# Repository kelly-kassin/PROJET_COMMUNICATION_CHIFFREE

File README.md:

# Projet_PCB_FISE_5A_POLYTECH : Communication IR Cryptée
# Binome : Kelly KASSIN & Youssef OMMI

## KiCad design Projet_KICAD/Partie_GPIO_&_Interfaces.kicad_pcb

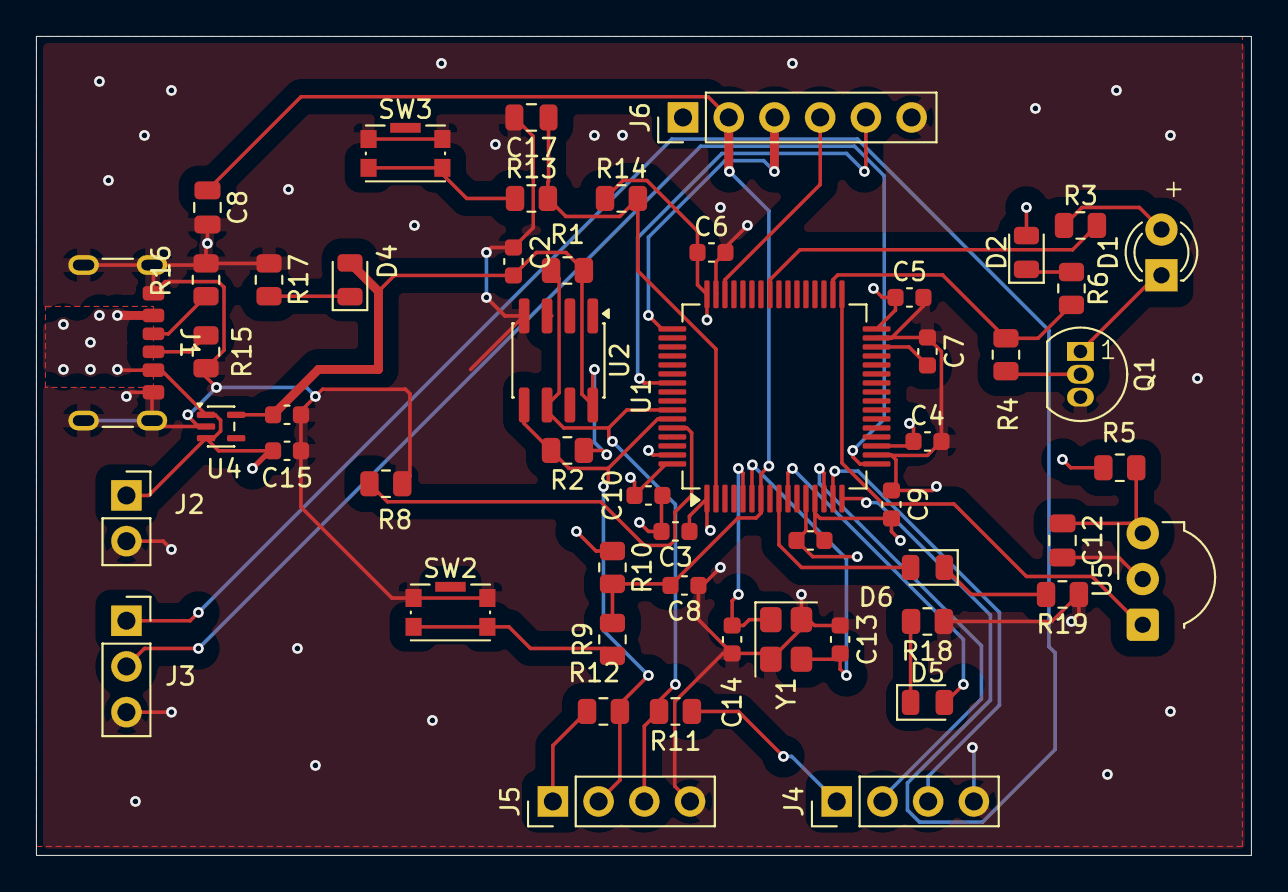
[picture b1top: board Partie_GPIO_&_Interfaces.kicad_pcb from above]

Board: 4 copper layers, 67.5 x 45.5 mm, 54 parts (0 on the bottom side), 35 nets.

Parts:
C2, C4, C5, C6, C8, C10, C11: 100nF; C_0603_1608Metric
C3: 4.7 uF; C_0603_1608Metric
C7: 4.7uF; C_0603_1608Metric
C8#2, C12, C17: 100nF; C_0805_2012Metric
C9: 2.2uF; C_0603_1608Metric
C13, C14: 20nF; C_0603_1608Metric
C15, C16: 1uF; C_0603_1608Metric
D1: TSAL4400; LED_D3.0mm_IRBlack
D2: LED GREEN; LED_0805_2012Metric
D4: LED RED; LED_0805_2012Metric
D5: LED YELLOW; LED_0805_2012Metric
D6: LED BLUE; LED_0805_2012Metric
J1: USB4125-GF-A-0190; USB_C_Receptacle_GCT_USB4125-xx-x-0190_6P_TopMnt_Horizontal
J2: Conn_01x02_Pin; PinSocket_1x02_P2.54mm_Vertical
J3: Conn_01x03_Pin; PinSocket_1x03_P2.54mm_Vertical
J4, J5: Conn_01x04_Pin; PinHeader_1x04_P2.54mm_Vertical
J6: Conn_01x06_Pin; PinHeader_1x06_P2.54mm_Vertical
Q1: 2N3906; TO-92_Inline
R1, R2, R11, R12: 4.7k; R_0805_2012Metric
R3, R4, R6, R9, R13, R17, R18, R19: 330; R_0805_2012Metric
R5: 100; R_0805_2012Metric
R8, R10, R14: 10k; R_0805_2012Metric
R15: 5.1K; R_0805_2012Metric
R16: 5.1k; R_0805_2012Metric
SW2, SW3: SW_Push; SW_Push_1P1T-SH_NO_CK_KMR2xxG
U1: STM32F413RGT6; LQFP-64_10x10mm_P0.5mm
U2: ATECC608C; SOIC-8_3.9x4.9mm_P1.27mm
U4: MIC5365-3.3YC5; SOT-353_SC-70-5
U5: TSOP34138; Vishay_MOLD-3Pin
Y1: Y322518.432MLBCX; Crystal_SMD_3225-4Pin_3.2x2.5mm

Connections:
+3.3V: C2.1, C3.1, C4.1, C5.1, C6.1, C9.1, C10.1, C11.1, C16.1, D2.2 (A), D4.2 (A), J4.1, J5.1, J6.1, R1.1, R2.1, R5.1, R10.1, R11.1, R12.1, R14.1, U1.1 (VBAT), U1.13 (VDDA), U1.19 (VDD), U1.32 (VDD), U1.48 (VDD), U1.64 (VDD), U2.8 (VCC), U4.5 (VOUT)
/GPIO_EXTI13: C17.1, R13.2, R14.2, U1.2 (PC13)
/HSE_IN: C14.2, U1.5 (PH0), Y1.1
/HSE_OUT: C13.2, U1.6 (PH1), Y1.3
/I2C1_SCL: J5.3, R1.2, R11.2, U1.58 (PB6), U2.6 (SCL)
/I2C1_SDA: J5.2, R2.2, R12.2, U1.59 (PB7), U2.5 (SDA)
/IR_RX: U1.33 (PB12), U5.1 (OUT)
/IR_TX: R4.2, R6.1, U1.34 (PB13)
/LED_IR_RX: D6.2 (A), U1.9 (PC1)
/NRST: C8.2, C8#2.1, J6.2, R9.2, R10.2, U1.7 (NRST)
/PWM: R3.2, U1.41 (PA8)
/SW_BOOT0: R8.1, U1.60 (BOOT0)
/SYS_JTDCK_SWDCLK: J6.3, U1.49 (PA14)
/SYS_JTDMS-SWDIO: J6.4, U1.46 (PA13)
/SYS_JTDO_SWDO: J6.5, U1.55 (PB3)
/UART2_RX: J3.2, U1.17 (PA3)
/UART2_TX: J3.1, U1.16 (PA2)
/UART4_RX: J4.3, U1.15 (PA1)
/UART4_TX: J4.2, U1.14 (PA0)
/VUSB: C15.1, J1.A9 (VBUS), J1.B9 (VBUS), J2.1, U4.1 (VIN), U4.3 (EN)
GND: C2.2, C3.2, C4.2, C5.2, C6.2, C7.2, C8.1, C8#2.2, C9.2, C10.2, C11.2, C12.2, C13.1, C14.1, C15.2, C16.2, C17.2, J1.A12 (GND), J1.B12 (GND), J1.SH (SHIELD), J2.2, J3.3, J4.4, J5.4, J6.6, Q1.3 (C), R8.2, R15.1, R16.1, R17.1, R18.1, R19.1, SW2.1, SW3.1, U1.12 (VSSA), U1.18 (VSS), U1.31 (VSS), U1.47 (VSS), U1.63 (VSS), U2.4 (GND), U4.2 (GND), U5.2 (GND), Y1.2 (G), Y1.4 (G)
unnamed: D1.2 (A), R3.1
unnamed: D1.1 (K), Q1.1 (E)
unnamed: D2.1 (K), R6.2
unnamed: D4.1 (K), R17.2
unnamed: D5.2 (A), U1.10 (PC2)
unnamed: D5.1 (K), R18.2
unnamed: D6.1 (K), R19.2
unnamed: J1.A5 (CC1), R16.2
unnamed: J1.B5 (CC2), R15.2
unnamed: Q1.2 (B), R4.1
unnamed: R9.1, SW2.2
unnamed: R13.1, SW3.2
unnamed: C7.1, U1.30 (VCAP_1)
unnamed: C12.1, R5.2, U5.3 (Vs)

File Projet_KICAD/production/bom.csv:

Designator,Footprint,Quantity,Value,LCSC Part #
"C10, C11, C2, C4, C5, C6, C8_2",0603,7,100nF,
"C12, C17, C8",0805,3,100nF,
"C13, C14",0603,2,20nF,
"C15, C16",0603,2,1uF,
C3,0603,1,4.7 uF,
C7,0603,1,4.7uF,
C9,0603,1,2.2uF,
D1,LED_D3.0mm_IRBlack,1,TSAL4400,
D2,0805,1,LED GREEN,C2297
D4,0805,1,LED RED,
D5,0805,1,LED YELLOW,
D6,0805,1,LED BLUE,
J1,USB_C_Receptacle_GCT_USB4125-xx-x-0190_6P_TopMnt_Horizontal,1,USB4125-GF-A-0190,
J2,PinSocket_1x02_P2.54mm_Vertical,1,Conn_01x02_Pin,C49661
J3,PinSocket_1x03_P2.54mm_Vertical,1,Conn_01x03_Pin,C22373889
"J4, J5",PinHeader_1x04_P2.54mm_Vertical,2,Conn_01x04_Pin,C32713270
J6,PinHeader_1x06_P2.54mm_Vertical,1,Conn_01x06_Pin,C32713272
Q1,TO-92_Inline,1,2N3906,
"R1, R2",0805,2,4.7k,C17673
"R10, R14, R8",0805,3,10k,C17414
"R11, R12",0805,2,4.7k,
"R13, R17, R18, R19, R3, R4, R6, R9",0805,8,330,C17630
R15,0805,1,5.1K,C26023
R16,0805,1,5.1k,C27834
R5,0805,1,100, C17408
"SW2, SW3",SW_Push_1P1T-SH_NO_CK_KMR2xxG,2,SW_Push,C269272
U1,LQFP-64_10x10mm_P0.5mm,1,STM32F413RGT6,
U2,SOIC-8_3.9x4.9mm_P1.27mm,1,ATECC608C,C25469796
U4,SOT-353_SC-70-5,1,MIC5365-3.3YC5,C3021118
U5,Vishay_MOLD-3Pin,1,TSOP34138,C118303
Y1,Crystal_SMD_3225-4Pin_3.2x2.5mm,1,Y322518.432MLBCX,

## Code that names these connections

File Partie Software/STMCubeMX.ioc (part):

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Mcu.Name=STM32F413R(G-H)Tx
Mcu.Package=LQFP64
Mcu.UserName=STM32F413RGTx
PA0.Mode=Asynchronous
PA0.Signal=UART4_TX
PA1.Mode=Asynchronous
PA1.Signal=UART4_RX
PA13.Mode=Trace_Asynchronous_SW
PA13.Signal=SYS_JTMS-SWDIO
PA14.Mode=Trace_Asynchronous_SW
PA14.Signal=SYS_JTCK-SWCLK
PA2.Mode=Asynchronous
PA2.Signal=USART2_TX
PA3.Mode=Asynchronous
PA3.Signal=USART2_RX
PA8.Signal=S_TIM1_CH1
PB12.Mode=Asynchronous
PB12.Signal=UART5_RX
PB13.Mode=Asynchronous
PB13.Signal=UART5_TX
PB3.Mode=Trace_Asynchronous_SW
PB3.Signal=SYS_JTDO-SWO
PB6.Mode=I2C
PB6.Signal=I2C1_SCL
PB7.Mode=I2C
PB7.Signal=I2C1_SDA
PC1.Signal=GPIO_Output
PC13.Signal=GPXTI13
PC2.GPIOParameters=GPIO_Label
PC2.GPIO_Label=LED_USER
PC2.Signal=GPIO_Output
PH0\ -\ OSC_IN.Mode=HSE-External-Oscillator
PH0\ -\ OSC_IN.Signal=RCC_OSC_IN
PH1\ -\ OSC_OUT.Mode=HSE-External-Oscillator
PH1\ -\ OSC_OUT.Signal=RCC_OSC_OUT
RCC.HSE_VALUE=18432000
board=custom
